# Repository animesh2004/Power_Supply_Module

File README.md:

# ⚡ Power Supply Module PCB (12V → 5V, 3.3V)

A compact dual-output linear voltage regulator module built using **LM7805** and **AMS1117-3.3**, designed in **KiCad**. The module takes an input of 12V DC and provides regulated 5V and 3.3V outputs with basic protection and filtering.

---

## 📦 Features

- ✅ Input Voltage: 9–15V DC
- ✅ Output 1: 5V (LM7805)
- ✅ Output 2: 3.3V (AMS1117)
- ✅ Input protection diode (1N4007)
- ✅ Electrolytic capacitor filtering
- ✅ Dual screw terminal output
- ✅ Standard THT components

---

## 🔧 Tools Used

| Tool     | Version   |
|----------|-----------|
| KiCad    | v7.x      |
| Git      | Yes       |
| Gerber Viewer | Yes  |

---

## 🧩 Components

| Reference | Component       | Value     |
|-----------|------------------|-----------|
| U1        | LM7805_T0220     | 5V Regulator |
| U2        | AMS1117-3.3      | 3.3V Regulator |
| D1        | 1N4007           | Diode |
| C1–C4     | Capacitor        | 10µF |
| J1, J2    | Conn_01x02       | Input/Output |

---

## 📂 Project Files

| File/Folder     | Description                   |
|-----------------|-------------------------------|
| `Schematic/`    | KiCad schematic `.kicad_sch`   |
| `PCB/`          | PCB layout `.kicad_pcb`        |
| `Gerbers/`      | Gerber files for fabrication   |
| `Images/`       | Renders and layout screenshots |
| `README.md`     | This file                      |

---

## 🛠️ How to Use

1. Connect 9–12V DC input to J1
2. Output 1 (J2 Pin 1): 5V
3. Output 2 (J2 Pin 2): 3.3V
4. Verify pinout before powering

---

## 📤 Gerber Export

Gerbers are available in `Gerbers/`. You can upload them directly to JLCPCB, PCBWay, or OSH Park.

---

## 📌 License

This project is open-source under the [MIT License](LICENSE).

---

## 🙋‍♂️ Author

**Animesh Tripathi**  
Designed with 💚 in KiCad  
[GitHub Profile](https://github.com/animesh2004)

---

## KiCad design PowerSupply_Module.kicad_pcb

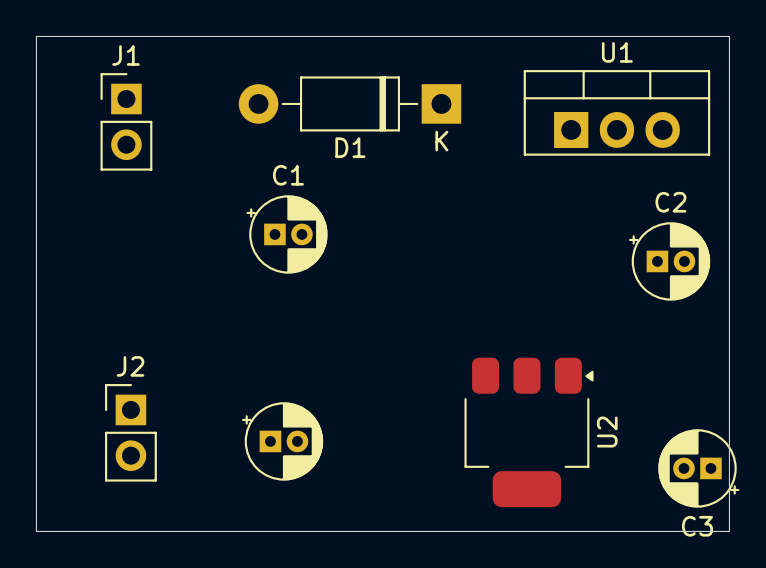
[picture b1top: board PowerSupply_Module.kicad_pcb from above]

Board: 2 copper layers, 38.5 x 27.5 mm, 9 parts (0 on the bottom side), 5 nets, no tracks yet.

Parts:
C1, C2, C3, C4: 10µF; CP_Radial_D4.0mm_P1.50mm
D1: 1N4007; D_DO-41_SOD81_P10.16mm_Horizontal
J1, J2: Conn_01x02; PinHeader_1x02_P2.54mm_Vertical
U1: LM7805_TO220; TO-220-3_Vertical
U2: AMS1117-3.3; SOT-223-3_TabPin2

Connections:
3V3: C4.1, J2.2, U2.2 (VO)
+5V: C2.1, C3.1, J2.1, U1.3 (VO), U2.3 (VI)
D1: C1.1, D1.1 (K), U1.1 (VI)
GND: C1.2, C2.2, C3.2, C4.2, J1.2, U1.2 (GND), U2.1 (GND)
VCC: D1.2 (A), J1.1
